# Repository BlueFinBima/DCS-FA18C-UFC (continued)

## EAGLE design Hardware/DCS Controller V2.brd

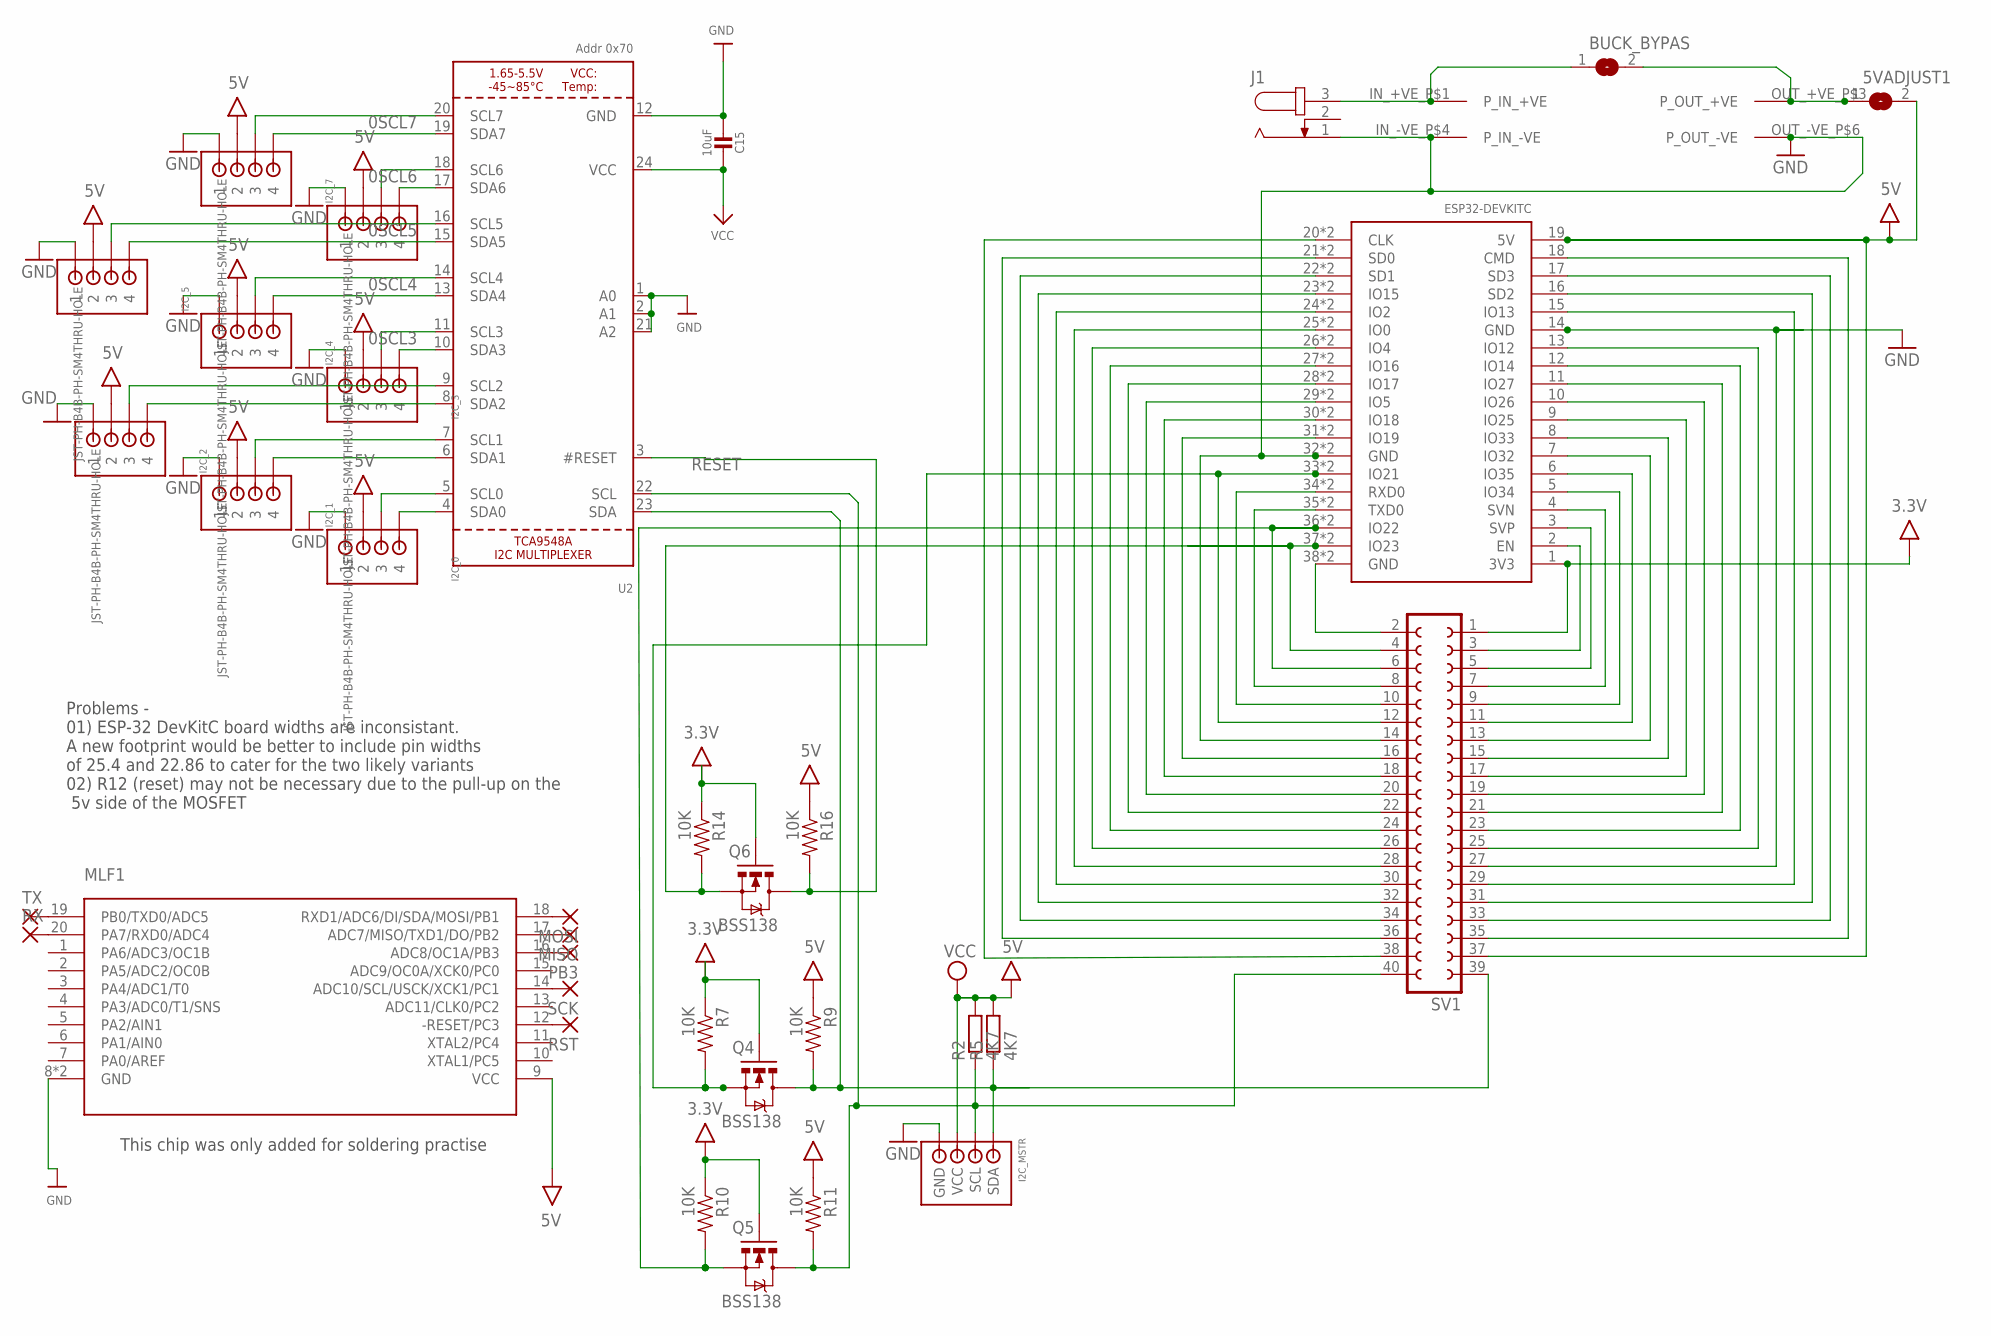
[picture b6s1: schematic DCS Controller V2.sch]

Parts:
5VADJUST1: SJ
BUCK_BYPAS: SJ
C15: 10uF; 0805-NO
I2C_0, I2C_1, I2C_2, I2C_3, I2C_4, I2C_5, I2C_6, I2C_7: JST-PH-B4B-PH-SM4THRU-HOLE; B4B-PH-SOLDER
I2C_MSTR: I2C_JST_CONNECTORTHROUGH_HOLE; B4B-PH-SOLDER
J1: JACK-PLUG0; SPC4077
MISO: 1,6/0,9
MLF1: ATTINY1634MLF20; MLF20
MOSI: 1,6/0,9
PB3: 1,6/0,9
Q4, Q5, Q6: BSS138; SOT23-3
R2, R5: 4K7; R0805
R7, R9, R10, R11, R14, R16: 10K; 0603-RES
RST: 1,6/0,9
RX: 1,6/0,9
SCK: 1,6/0,9
SV1: FE20-2
TX: 1,6/0,9
U2: Addr 0x70; TSSOP24
U$26: EBAY_BUCK_CONVERTERMODULE; BUCK_CONVERTER
U$34: ESP32DEVKITC; ESP32-DEVKITC

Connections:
0SCL1: I2C_2.P3 (3), U2.9 (SCL2)
0SCL3: I2C_3.P3 (3), U2.11 (SCL3)
0SCL4: I2C_4.P3 (3), U2.14 (SCL4)
0SCL5: I2C_5.P3 (3), U2.16 (SCL5)
0SCL6: I2C_6.P3 (3), U2.18 (SCL6)
0SCL7: I2C_7.P3 (3), U2.20 (SCL7)
3.3V: SV1.1, U$34.1 (3V3)
3V3: Q4.1 (G), Q5.1 (G), Q6.1 (G), R7.1, R10.1, R14.1
5V: 5VADJUST1.2, C15.1, I2C_0.P2 (2), I2C_1.P2 (2), I2C_2.P2 (2), I2C_3.P2 (2), I2C_4.P2 (2), I2C_5.P2 (2), I2C_6.P2 (2), I2C_7.P2 (2), MLF1.9 (VCC), R9.1, R11.1, R16.1, SV1.37, U2.24 (VCC), U$34.19 (5V)
GND: C15.2, I2C_0.P1 (1), I2C_1.P1 (1), I2C_2.P1 (1), I2C_3.P1 (1), I2C_4.P1 (1), I2C_5.P1 (1), I2C_6.P1 (1), I2C_7.P1 (1), I2C_MSTR.P1 (GND), J1.1, MLF1.8 (GND), MLF1.GND, SV1.14, SV1.27, U2.1 (A0), U2.2 (A1), U2.12 (GND), U2.21 (A2), U$26.IN_-VE_P$4 (P_IN_-VE), U$26.OUT_-VE_P$6 (P_OUT_-VE), U$34.14 (GND), U$34.32 (GND), U$34.GND_32 (GND)
I2C_0: I2C_MSTR.P4 (SDA), Q4.3 (D), R5.1, R9.2, SV1.39, U2.23 (SDA)
I2C_1: I2C_MSTR.P3 (SCL), Q5.3 (D), R2.1, R11.2, SV1.40, U2.22 (SCL)
unnamed: SV1.3, U$34.2 (EN)
unnamed: SV1.5, U$34.3 (SVP)
unnamed: SV1.7, U$34.4 (SVN)
unnamed: SV1.9, U$34.5 (IO34)
unnamed: SV1.11, U$34.6 (IO35)
unnamed: SV1.13, U$34.7 (IO32)
unnamed: SV1.15, U$34.8 (IO33)
unnamed: SV1.17, U$34.9 (IO25)
unnamed: SV1.19, U$34.10 (IO26)
unnamed: SV1.21, U$34.11 (IO27)
unnamed: SV1.23, U$34.12 (IO14)
unnamed: SV1.25, U$34.13 (IO12)
unnamed: SV1.29, U$34.15 (IO13)
unnamed: SV1.31, U$34.16 (SD2)
unnamed: SV1.33, U$34.17 (SD3)
unnamed: SV1.35, U$34.18 (CMD)
unnamed: SV1.2, U$34.38 (GND), U$34.GND_38 (GND)
unnamed: SV1.8, U$34.35 (TXD0), U$34.TXD0
unnamed: SV1.10, U$34.34 (RXD0), U$34.RXD0
unnamed: SV1.16, U$34.31 (IO19), U$34.IO19
unnamed: SV1.18, U$34.30 (IO18), U$34.IO18
unnamed: SV1.20, U$34.29 (IO5), U$34.IO5
unnamed: SV1.22, U$34.28 (IO17), U$34.IO17
unnamed: SV1.24, U$34.27 (IO16), U$34.IO16
unnamed: SV1.26, U$34.26 (IO4), U$34.IO4
unnamed: SV1.28, U$34.25 (IO0), U$34.IO0
unnamed: SV1.30, U$34.24 (IO2), U$34.IO2
unnamed: SV1.32, U$34.23 (IO15), U$34.IO15
unnamed: SV1.34, U$34.22 (SD1), U$34.SD1
unnamed: SV1.36, U$34.21 (SD0), U$34.SD0
unnamed: SV1.38, U$34.20 (CLK), U$34.CLK
unnamed: MLF1.18 (RXD1/ADC6/DI/SDA/MOSI/PB1), MOSI.1
unnamed: BUCK_BYPAS.1, J1.3, U$26.IN_+VE_P$1 (P_IN_+VE)
unnamed: 5VADJUST1.1, BUCK_BYPAS.2, U$26.OUT_+VE_P$3 (P_OUT_+VE)
unnamed: MLF1.12 (-RESET/PC3), RST.1
unnamed: MLF1.14 (ADC10/SCL/USCK/XCK1/PC1), SCK.1
unnamed: MISO.1, MLF1.17 (ADC7/MISO/TXD1/DO/PB2)
unnamed: I2C_7.P4 (4), U2.19 (SDA7)
unnamed: I2C_0.P4 (4), U2.4 (SDA0)
unnamed: I2C_0.P3 (3), U2.5 (SCL0)
unnamed: I2C_1.P4 (4), U2.6 (SDA1)
unnamed: MLF1.16 (ADC8/OC1A/PB3), PB3.1
unnamed: I2C_1.P3 (3), U2.7 (SCL1)
unnamed: I2C_2.P4 (4), U2.8 (SDA2)
unnamed: I2C_6.P4 (4), U2.17 (SDA6)
unnamed: I2C_5.P4 (4), U2.15 (SDA5)
unnamed: I2C_4.P4 (4), U2.13 (SDA4)
unnamed: I2C_3.P4 (4), U2.10 (SDA3)
unnamed: MLF1.19 (PB0/TXD0/ADC5), TX.1
unnamed: MLF1.20 (PA7/RXD0/ADC4), RX.1
unnamed: Q6.2 (S), R14.2, SV1.4, U$34.37 (IO23), U$34.IO23
RESET: Q6.3 (D), R16.2, U2.3 (#RESET)
SCL3V1: Q5.2 (S), R10.2, SV1.6, U$34.36 (IO22), U$34.IO22
SDA3V2: Q4.2 (S), R7.2, SV1.12, U$34.33 (IO21), U$34.IO21
VCC: I2C_MSTR.P2 (VCC), R2.2, R5.2

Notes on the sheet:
Problems - 01) ESP-32 DevKitC board widths are inconsistant. A new footprint would be better to include pin widths of 25.4 and 22.86 to cater for the two likely variants 02) R12 (reset) may not be necessary due to the pull-up on the 5v side of the MOSFET
This chip was only added for soldering practise

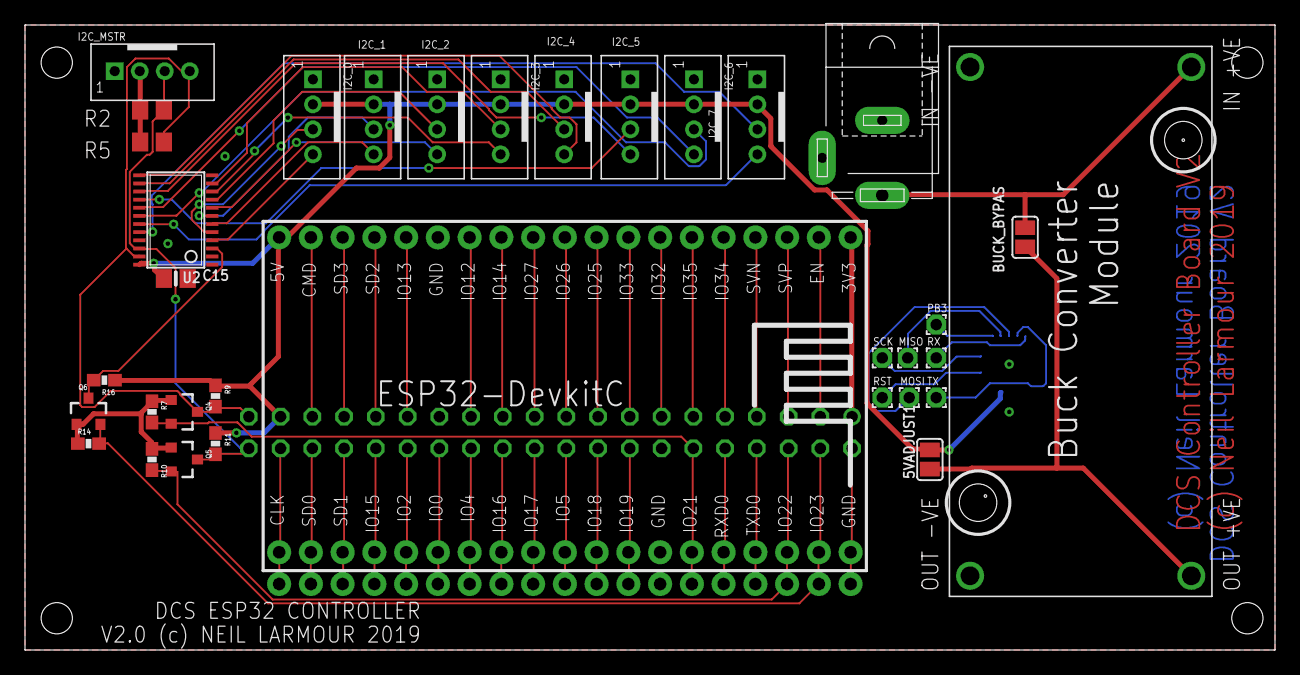
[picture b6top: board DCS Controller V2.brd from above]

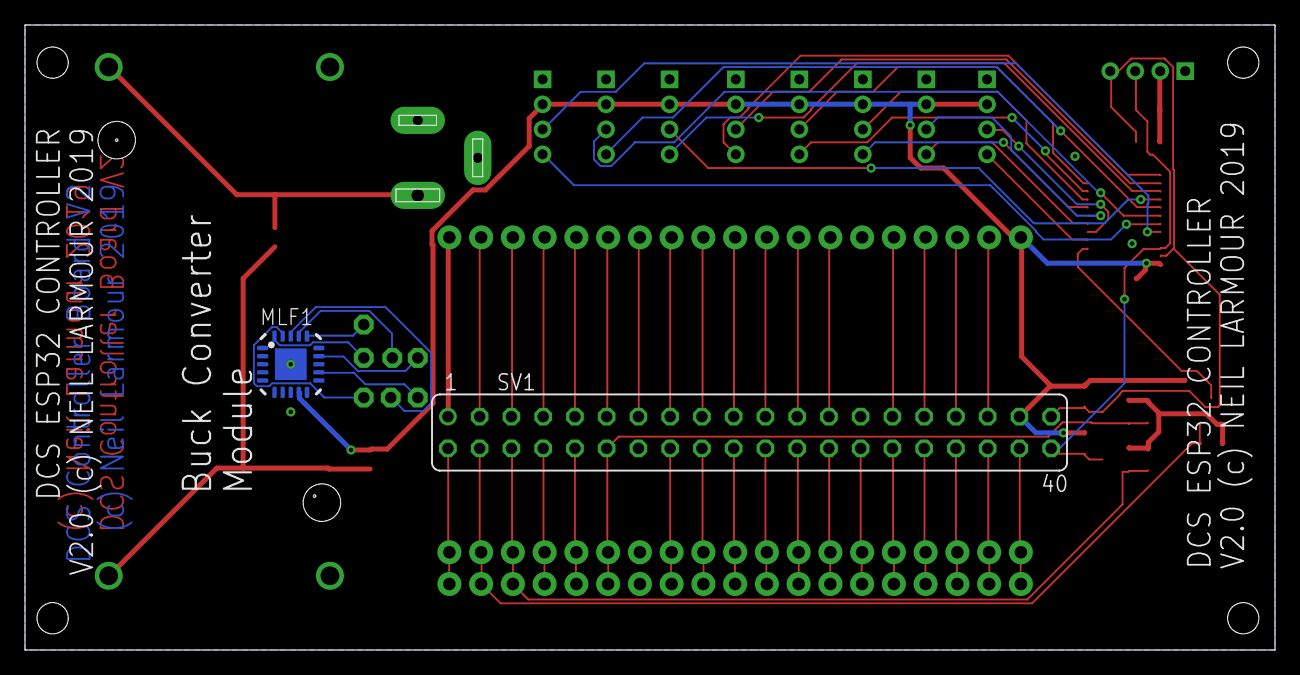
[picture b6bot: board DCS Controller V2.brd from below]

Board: 2 copper layers, 100.0 x 50.0 mm, 36 parts (2 on the bottom side), 67 nets.

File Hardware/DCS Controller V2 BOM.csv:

"Part";"Value";"Device";"Package";"Description";"MF";"MPN";"OC_FARNELL";"OC_NEWARK";"SPICEPREFIX";
"5VADJUST1";"";"SJ";"SJ";"SMD solder JUMPER";"";"";"";"";"";
"BUCK_BYPAS";"";"SJ";"SJ";"SMD solder JUMPER";"";"";"";"";"";
"C15";"10uF";"CAP_CERAMIC0805-NOOUTLINE";"0805-NO";"Ceramic Capacitors";"";"";"";"";"";
"I2C_0";"JST-PH-B4B-PH-SM4THRU-HOLE";"JST-PH-B4B-PH-SM4THRU-HOLE";"B4B-PH-SOLDER";"JST PH 4 Pin (2.00")";"";"";"";"";"";
"I2C_1";"JST-PH-B4B-PH-SM4THRU-HOLE";"JST-PH-B4B-PH-SM4THRU-HOLE";"B4B-PH-SOLDER";"JST PH 4 Pin (2.00")";"";"";"";"";"";
"I2C_2";"JST-PH-B4B-PH-SM4THRU-HOLE";"JST-PH-B4B-PH-SM4THRU-HOLE";"B4B-PH-SOLDER";"JST PH 4 Pin (2.00")";"";"";"";"";"";
"I2C_3";"JST-PH-B4B-PH-SM4THRU-HOLE";"JST-PH-B4B-PH-SM4THRU-HOLE";"B4B-PH-SOLDER";"JST PH 4 Pin (2.00")";"";"";"";"";"";
"I2C_4";"JST-PH-B4B-PH-SM4THRU-HOLE";"JST-PH-B4B-PH-SM4THRU-HOLE";"B4B-PH-SOLDER";"JST PH 4 Pin (2.00")";"";"";"";"";"";
"I2C_5";"JST-PH-B4B-PH-SM4THRU-HOLE";"JST-PH-B4B-PH-SM4THRU-HOLE";"B4B-PH-SOLDER";"JST PH 4 Pin (2.00")";"";"";"";"";"";
"I2C_6";"JST-PH-B4B-PH-SM4THRU-HOLE";"JST-PH-B4B-PH-SM4THRU-HOLE";"B4B-PH-SOLDER";"JST PH 4 Pin (2.00")";"";"";"";"";"";
"I2C_7";"JST-PH-B4B-PH-SM4THRU-HOLE";"JST-PH-B4B-PH-SM4THRU-HOLE";"B4B-PH-SOLDER";"JST PH 4 Pin (2.00")";"";"";"";"";"";
"I2C_MSTR";"";"I2C_JST_CONNECTORTHROUGH_HOLE";"B4B-PH-SOLDER";"";"";"";"";"";"";
"J1";"";"JACK-PLUG0";"SPC4077";"DC POWER JACK";"";"";"unknown";"unknown";"";
"MISO";"";"1,6/0,9";"1,6/0,9";"THROUGH-HOLE PAD";"";"";"";"";"";
"MLF1";"ATTINY1634MLF20";"ATTINY1634MLF20";"MLF20";"";"";"";"";"";"";
"MOSI";"";"1,6/0,9";"1,6/0,9";"THROUGH-HOLE PAD";"";"";"";"";"";
"PB3";"";"1,6/0,9";"1,6/0,9";"THROUGH-HOLE PAD";"";"";"";"";"";
"Q4";"BSS138";"MOSFET-NCHANNELSMD";"SOT23-3";"";"";"";"";"";"";
"Q5";"BSS138";"MOSFET-NCHANNELSMD";"SOT23-3";"";"";"";"";"";"";
"Q6";"BSS138";"MOSFET-NCHANNELSMD";"SOT23-3";"";"";"";"";"";"";
"R2";"4K7";"R-EU_R0805";"R0805";"RESISTOR, European symbol";"";"";"";"";"R";
"R5";"4K7";"R-EU_R0805";"R0805";"RESISTOR, European symbol";"";"";"";"";"R";
"R7";"10K";"RESISTOR0603-RES";"0603-RES";"Resistor";"";"";"";"";"";
"R9";"10K";"RESISTOR0603-RES";"0603-RES";"Resistor";"";"";"";"";"";
"R10";"10K";"RESISTOR0603-RES";"0603-RES";"Resistor";"";"";"";"";"";
"R11";"10K";"RESISTOR0603-RES";"0603-RES";"Resistor";"";"";"";"";"";
"R14";"10K";"RESISTOR0603-RES";"0603-RES";"Resistor";"";"";"";"";"";
"R16";"10K";"RESISTOR0603-RES";"0603-RES";"Resistor";"";"";"";"";"";
"RST";"";"1,6/0,9";"1,6/0,9";"THROUGH-HOLE PAD";"";"";"";"";"";
"RX";"";"1,6/0,9";"1,6/0,9";"THROUGH-HOLE PAD";"";"";"";"";"";
"SCK";"";"1,6/0,9";"1,6/0,9";"THROUGH-HOLE PAD";"";"";"";"";"";
"SV1";"";"FE20-2";"FE20-2";"FEMALE HEADER";"";"";"unknown";"unknown";"";
"TX";"";"1,6/0,9";"1,6/0,9";"THROUGH-HOLE PAD";"";"";"";"";"";
"U$26";"EBAY_BUCK_CONVERTERMODULE";"EBAY_BUCK_CONVERTERMODULE";"BUCK_CONVERTER";"";"";"";"";"";"";
"U$34";"ESP32DEVKITC";"ESP32DEVKITC";"ESP32-DEVKITC";"";"";"";"";"";"";
"U2";"Addr 0x70";"TCA9548A";"TSSOP24";"TCA9548A I2C Multiplexer";"";"";"";"";"X";

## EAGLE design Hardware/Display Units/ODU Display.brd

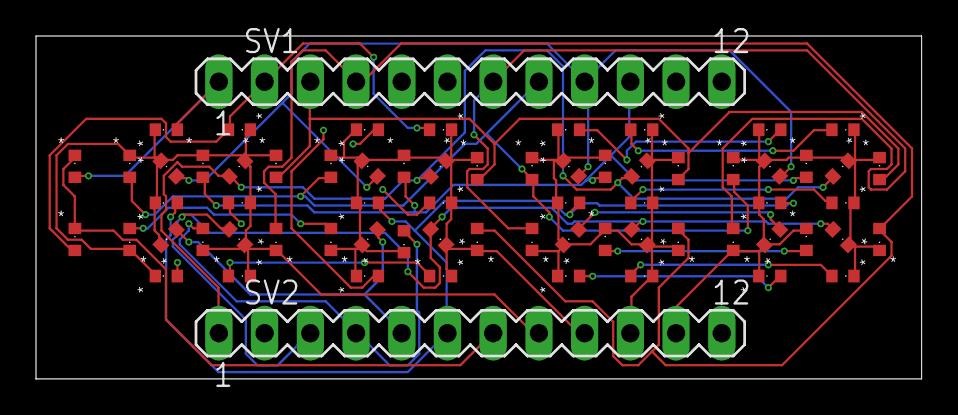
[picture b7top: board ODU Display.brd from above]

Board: 4 copper layers, 49.2 x 19.1 mm, 68 parts (0 on the bottom side), 21 nets.

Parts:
LED_A1, LED_A2, LED_A3, LED_A4: CHIPLED_0402
LED_B1, LED_B2, LED_B3, LED_B4: CHIPLED_0402
LED_C1, LED_C2, LED_C3, LED_C4: CHIPLED_0402
LED_D1, LED_D2, LED_D3, LED_D4: CHIPLED_0402
LED_E1, LED_E2, LED_E3, LED_E4: CHIPLED_0402
LED_F1, LED_F2, LED_F3, LED_F4: CHIPLED_0402
LED_G1, LED_G2, LED_G3, LED_G4: CHIPLED_0402
LED_H1, LED_H2, LED_H3, LED_H4: CHIPLED_0402
LED_K1, LED_K2, LED_K3, LED_K4: CHIPLED_0402
LED_M1, LED_M2, LED_M3, LED_M4: CHIPLED_0402
LED_N1, LED_N2, LED_N3, LED_N4: CHIPLED_0402
LED_P1, LED_P2, LED_P3, LED_P4: CHIPLED_0402
LED_R1, LED_R2, LED_R3, LED_R4: CHIPLED_0402
LED_S1, LED_S2, LED_S3, LED_S4: CHIPLED_0402
LED_SEL1, LED_SEL2: CHIPLED_0402
LED_T1, LED_T2, LED_T3, LED_T4: CHIPLED_0402
LED_U1, LED_U2, LED_U3, LED_U4: CHIPLED_0402
SV1, SV2: MA12-1

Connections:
K0: LED_SEL1.C, LED_SEL2.C, SV2.7
K1: LED_A1.C, LED_B1.C, LED_C1.C, LED_D1.C, LED_E1.C, LED_F1.C, LED_G1.C, LED_H1.C, LED_K1.C, LED_M1.C, LED_N1.C, LED_P1.C, LED_R1.C, LED_S1.C, LED_T1.C, LED_U1.C, SV2.8
K2: LED_A2.C, LED_B2.C, LED_C2.C, LED_D2.C, LED_E2.C, LED_F2.C, LED_G2.C, LED_H2.C, LED_K2.C, LED_M2.C, LED_N2.C, LED_P2.C, LED_R2.C, LED_S2.C, LED_T2.C, LED_U2.C, SV2.9
K3: LED_A3.C, LED_B3.C, LED_C3.C, LED_D3.C, LED_E3.C, LED_F3.C, LED_G3.C, LED_H3.C, LED_K3.C, LED_M3.C, LED_N3.C, LED_P3.C, LED_R3.C, LED_S3.C, LED_T3.C, LED_U3.C, SV2.10
K4: LED_A4.C, LED_B4.C, LED_C4.C, LED_D4.C, LED_E4.C, LED_F4.C, LED_G4.C, LED_H4.C, LED_K4.C, LED_M4.C, LED_N4.C, LED_P4.C, LED_R4.C, LED_S4.C, LED_T4.C, LED_U4.C, SV2.11
SEG_A: LED_A1.A, LED_A2.A, LED_A3.A, LED_A4.A, LED_SEL1.A, SV1.1
SEG_B: LED_B1.A, LED_B2.A, LED_B3.A, LED_B4.A, LED_SEL2.A, SV1.2
SEG_C: LED_C1.A, LED_C2.A, LED_C3.A, LED_C4.A, SV1.3
SEG_D: LED_D1.A, LED_D2.A, LED_D3.A, LED_D4.A, SV1.4
SEG_E: LED_E1.A, LED_E2.A, LED_E3.A, LED_E4.A, SV1.5
SEG_F: LED_F1.A, LED_F2.A, LED_F3.A, LED_F4.A, SV1.6
SEG_G: LED_G1.A, LED_G2.A, LED_G3.A, LED_G4.A, SV1.7
SEG_H: LED_H1.A, LED_H2.A, LED_H3.A, LED_H4.A, SV1.8
SEG_K: LED_K1.A, LED_K2.A, LED_K3.A, LED_K4.A, SV1.9
SEG_M: LED_M1.A, LED_M2.A, LED_M3.A, LED_M4.A, SV1.10
SEG_N: LED_N1.A, LED_N2.A, LED_N3.A, LED_N4.A, SV2.1
SEG_P: LED_P1.A, LED_P2.A, LED_P3.A, LED_P4.A, SV2.2
SEG_R: LED_R1.A, LED_R2.A, LED_R3.A, LED_R4.A, SV2.3
SEG_S: LED_S1.A, LED_S2.A, LED_S3.A, LED_S4.A, SV2.4
SEG_T: LED_T1.A, LED_T2.A, LED_T3.A, LED_T4.A, SV2.5
SEG_U: LED_U1.A, LED_U2.A, LED_U3.A, LED_U4.A, SV2.6

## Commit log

2019-03-25 Initial Drop of S/W, H/W, & 3D Models
    This is the first drop of code and files for the Hardware UFC I use with DCS World.
2019-03-25 Create Export.lua
    This islua code to communicate with the UFC.
2019-03-25 Initial Readme
2019-03-26 Production STLs Added
    UFC Back, Front and Facia STLs added which were the ones I used and printed in PET-G. Also included the keycap mitre I used to cut the keycaps down to size with a razor saw.
2020-08-23 Addition of new laser cut parts for the enclosure
    Changes to use 3mm black acrylic to create the enclosure.
2020-08-27 Adjusting gitignore
2020-08-27 Added missing FA18CufcDisplay Library
2020-08-27 Change the defauly port number ot 9089
2020-08-31 Added missing FA18CufcDisplay. Changed to mask left digit instead of right on the primary dispaly Network configuration using IotWebConf Change UDP port to 9089 Removed encoder debugging
2020-10-09 Schematic PDF and updated control program
    Control program improvement to allow IP setting at set-up.
2020-10-09 Updated Readme with Image
2020-10-12 Adding in WiFiInfo.h
2020-10-13 More Comments and Function Prototypes
    A little more comments based on conversations about the included libraries.
    Created function prototypes for the ISR's which seem to be needed for the compiler used by the Arduino IDE.
2020-10-28 Changes to code for Comm1 and DCS scripting
2020-10-29 Corrections for incorrect parts in BoM and labeled on Schematic
2020-11-03 Implemented mechanism to elect to reconfigure via access point (for 2 minutes) if the UFC is reset with either the I/P button or ODU1 button pressed.
2020-11-03 Update WiFiInfo.h
    Remove semi-colons from WIFI credientials
2020-11-06 Limited desk clock function
2020-11-07 Fix for https://github.com/BlueFinBima/DCS-FA18C-UFC/issues/7
2020-11-11 Add STLs for MX Keycaps
2020-11-19 Adjusted 3D models dor ODU keys and Comm Selector
2021-02-06 Move the scratchpad back to the original position with the right-most digit masked instead of the left-most.
2021-07-02 Pre-V3 work and Readme update
2021-10-30 Initial commit for basic AV-8B functionality.
2021-10-30 AV-8B UFC specific export.lua file added
2021-11-19 Add PDF for the controller and changes to the software.
2024-06-20 Create LICENSE
